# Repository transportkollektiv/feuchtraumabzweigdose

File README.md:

# Feuchtraumabzweigdose

This PCB is meant to function as an experimental playground for the [OpenBike](https://ulm.dev/projects/openbike/) project. It integrates WiFi and Bluetooth via the ESP32 MCU and LoRaWAN through the ubiquitous RFM95W modem. It also has a dedicated header for a gyro module as well as a switchable power supply for GNSS/GPS modules that can be switched off for deep sleep. It exposes a shared SPI bus, two serial lines and all unused pins of the ESP32, with several RTC interrupt methods available in hardware. A dedicated dynamo-to-Li+ charger as well as an efficient 3.3V LDO to supply the logic can be populated optionally. 

All in all it is an attempt to migrate most of the functionality of a TTGO T-Beam while being able to run days or weeks on end on one 18650 cell while mostly being in deep sleep. The T-Beam will usually deplete the cell within 30 hours.

For full functional documentation see [`docs/feuchtraumabzweigdose_docs.pdf`](docs/feuchtraumabzweigdose_docs.pdf).

The project is named Feuchtraumabzweigdose because it is meant to fit snugly into a waterproof junction box – or Feuchtraumabzweigdose in German :D

## Known issues in v0.1

* stk forgot the pullup resistors on the BOOT and RESET buttons respectively. This can be mitigated through botch wire.
* ~stk probably also forgot a pulldown resistor for the interrupt on the MPU9250 breakout header. Botch wire, again.~ When using the MPU9250 as a wakeup source, at least within the Arduino framework for quick and dirty first prototyping, apparently you have to actively wait for a bit between setting an external wakeup source and actually putting the device to sleep.
* as of now, the circuit has no undervoltage protection for the 18650. Use protected cells, if possible
* The voltage divider that is meant to be read by the ADC is 1:10, which brings down the measurable range of values quite a bit. Replace R3 with a 1M resistor to bring it down to a simple 1:1 divider, but this also increases the power draw during deep sleep.
* The 10k resistor at the MCP73832's `PROG` pin (R2) limits charging current to 100mA. ~Might want to replace this with maybe a 2k resistor (500 mA) or something in between~ This should not be increased too much
* in v0.1, the MOSFET switching the external power for the GPS (Q1) has pins 2 and 3 switched. A quick fix is to rotate it 180 degrees and switch the Source and Drain pins, then connect the Gate pin to one pad of the unpopulated C1 at the R1/R5 junction. See [this image for reference.](docs/botch-q1.jpg)

## Firmware

See [stadtulm/feuchtraumabzweigdose-testing](https://github.com/stadtulm/feuchtraumabzweigdose-testing)

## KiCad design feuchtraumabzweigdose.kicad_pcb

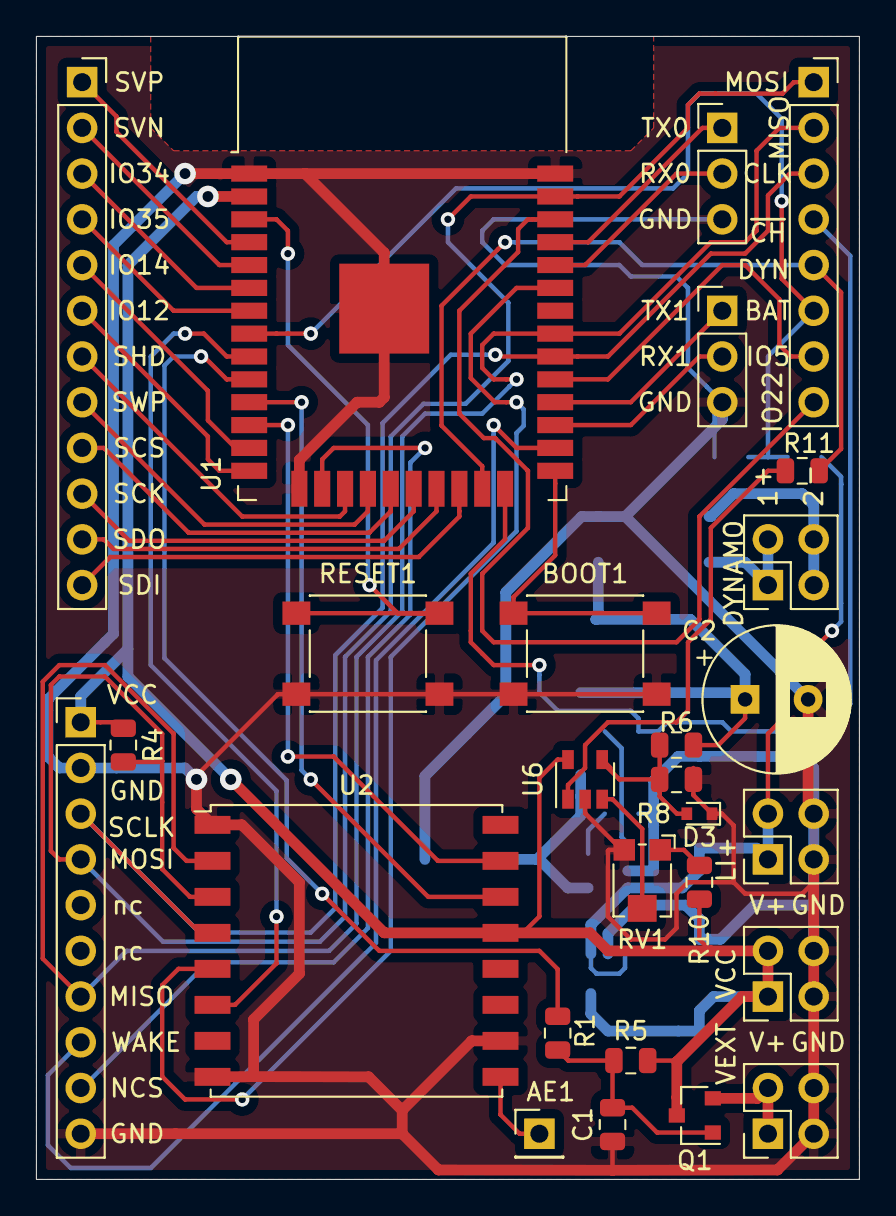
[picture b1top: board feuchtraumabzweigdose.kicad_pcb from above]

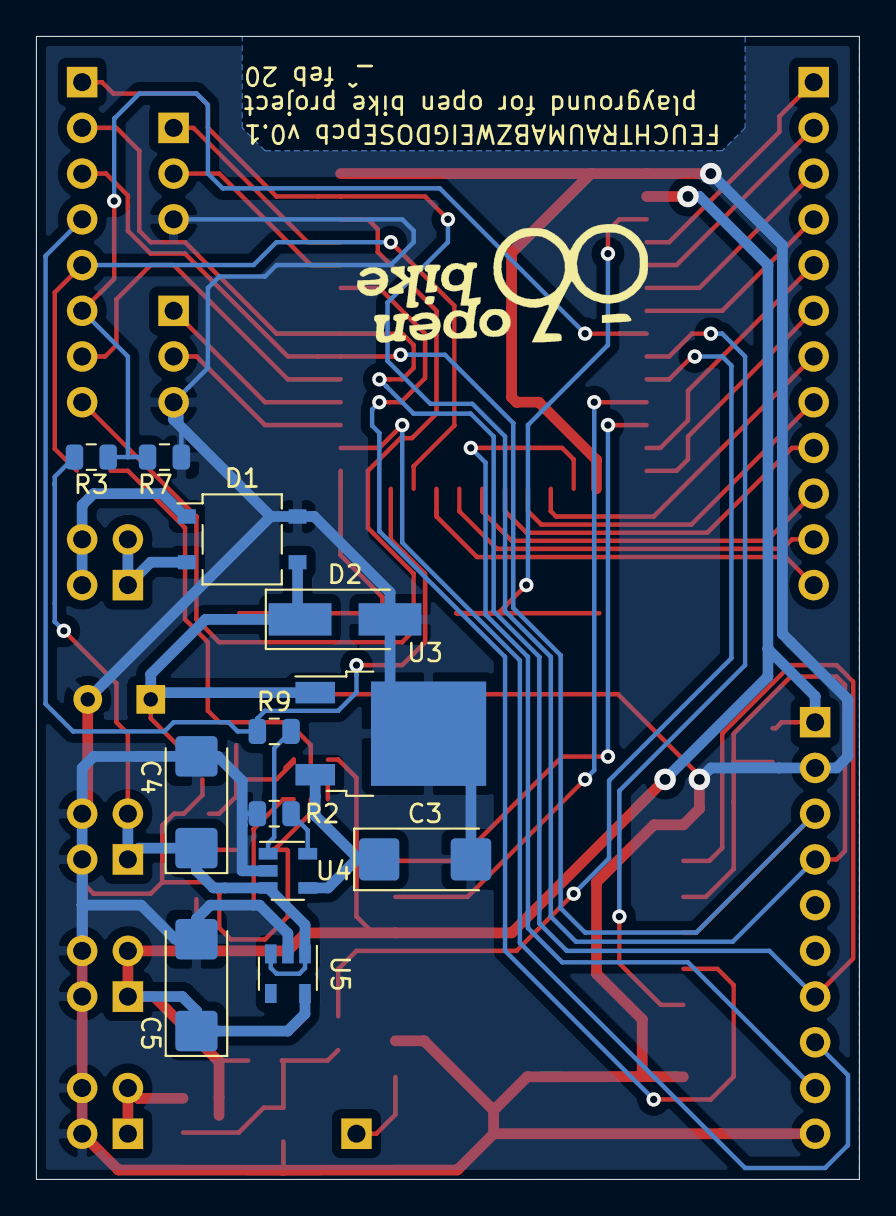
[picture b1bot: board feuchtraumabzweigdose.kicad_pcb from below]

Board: 2 copper layers, 45.7 x 63.5 mm, 39 parts (12 on the bottom side), 49 nets.

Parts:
AE1: Antenna; PinHeader_1x01_P2.54mm_Vertical
BOOT1: SW_Push; SW_Push_1P1T_NO_6x6mm_H9.5mm
C1: opt; C_0805_2012Metric
C2: 470u; CP_Radial_D8.0mm_P3.50mm
C3, C4: 4.7u; CP_EIA-6032-28_Kemet-C_Pad2.25x2.35mm_HandSolder
C5: 10u; CP_EIA-6032-28_Kemet-C_Pad2.25x2.35mm_HandSolder
D1: MB2S; TO-269AA
D2: 22V; D_SMA_Handsoldering
D3: 1N914WT; D_SOD-523
DYNAMO: DYN; PinHeader_2x02_P2.54mm_Vertical
J2, J5: Conn_01x03; PinHeader_1x03_P2.54mm_Vertical
J3: Conn_01x10; PinHeader_1x10_P2.54mm_Vertical
J8: Conn_01x12; PinSocket_1x12_P2.54mm_Vertical
J9: Conn_01x08; PinSocket_1x08_P2.54mm_Vertical
LI+: LI+; PinHeader_2x02_P2.54mm_Vertical
Q1: DMG2301L; SOT-23
R1, R2, R4, R9, R11: 10k; R_0805_2012Metric
R3, R10: 9M; R_0805_2012Metric
R5, R7, R8: 1M; R_0805_2012Metric
R6: 47k; R_0805_2012Metric
RESET1: SW_Push; SW_Push_1P1T_NO_6x6mm_H9.5mm
RV1: 1M; Potentiometer_Bourns_TC33X_Vertical
U1: ESP32-WROOM-32
U2: RFM95W-868S2; HOPERF_RFM9XW_SMD
U3: LF50_TO220; TO-252-2
U4: MCP73832-2-OT; SOT-23-5
U5: TLV75733PDBV; SOT-23-5
U6: TS881xLx; SOT-23-5
VCC: VC; PinHeader_2x02_P2.54mm_Vertical
VEXT: VEXT; PinHeader_2x02_P2.54mm_Vertical

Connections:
/power/WAKE: R11.2, U6.1
/power/~CHRG: R9.2, U4.1
ADC_BATT: J9.6, R3.2, R7.1, U1.8
DYNAMO: J9.5, R11.1, U1.23
ESP_SCK: J8.10, U1.20
ESP_SCS: J8.9, U1.19
ESP_SDI: J8.12, U1.22
ESP_SDO: J8.11, U1.21
ESP_SHD: J8.7, U1.17
ESP_SWP: J8.8, U1.18
GND: BOOT1.2, C1.1, C2.2, C3.2, C4.2, C5.2, D1.4, D2.2, D3.1, J2.3, J3.2, J3.10, J5.3, LI+.3, LI+.4, R2.2, R6.2, R7.2, RESET1.1, RV1.3, U1.1, U1.15, U1.38, U1.39, U2.1, U2.8, U2.10, U3.2, U4.2, U5.2, U6.2, VCC.3, VCC.4, VEXT.3, VEXT.4
GYRO_WAKE: J3.8, U1.26
IO5: J9.7, U1.29
IO12: J8.6, U1.14
IO14: J8.5, U1.13
IO22: J9.8, U1.36
IO34: J8.3, U1.6
IO35: J8.4, U1.7
MISO: J3.7, J9.2, U1.31, U2.2
MOSI: J3.4, J9.1, R4.2, U1.37, U2.3
MPU_NCS: J3.9, U1.16
unnamed: AE1.1, U2.9
unnamed: BOOT1.1, U1.25
unnamed: C1.2, Q1.1, R1.1, R5.1
unnamed: C2.1, D1.3, D2.1, R8.1, U3.1
unnamed: C3.1, U3.3, U4.4
unnamed: C4.1, LI+.1, LI+.2, R3.1, U4.3, U5.1, U5.3
unnamed: D1.1, DYNAMO.3, DYNAMO.4
unnamed: D1.2, DYNAMO.1, DYNAMO.2
unnamed: D3.2, R6.1, R8.2, U6.4
unnamed: J2.1, U1.35
unnamed: J2.2, U1.34
unnamed: R2.1, U4.5
unnamed: R10.2, RV1.1
unnamed: RESET1.2, U1.3
unnamed: RV1.2, U6.3
RFM_DIO0: U1.11, U2.14
RFM_DIO1: U1.12, U2.15
RFM_NSS: U1.33, U2.5
RFM_RESET: U1.9, U2.6
RX1: J5.2, U1.27
SCLK: J3.3, J9.3, U1.30, U2.4
SVN: J8.2, U1.5
SVP: J8.1, U1.4
TX1: J5.1, U1.28
VCC: C5.1, J3.1, Q1.3, R4.1, R5.2, R10.1, U1.2, U2.13, U5.5, U6.5, VCC.1, VCC.2
VEXT: Q1.2, VEXT.1, VEXT.2
~CHARGE: J9.4, R9.1, U1.24
~VEXT_ON: R1.2, U1.10

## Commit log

2020-02-23 first run but with fixed silkscreen :)
2020-02-23 added license, fixed file name collision
2020-02-23 added readme and specified some field values
2020-02-23 debloated
2020-02-23 forgot to render
2020-02-23 reformatted a bit
2020-02-23 fixed link to doc
2020-03-19 added voltage divider and PROG issues
2020-04-22 added images for documentation of v0.1
2020-04-22 updated documentation for v0.1, fix for Q1
2021-06-07 Readme: Add link to firmware
